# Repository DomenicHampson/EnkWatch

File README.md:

# EnkWatch
<h6>Note: I am still in the process of writing the firmware and mechanical design</h6>
<h4>Custom designed e-ink smartwatch with 2 weeks of battery life! The watch uses a PIC MCU with a built in RTC module and attached to an external temperature and humidity
    sensor via SPI bus to display data to the user on a e-ink screen. The time/date and off-times are set, aswell as the sensors calibrated through USB 2.0 by the user through
    python scripts. The watch is enclosed is a 3D printed shell designed using solidworks.</h4>

<h4><u>Features</u></h4>
<ul>
  <li>2 Week Battery Life: Use low power components and efficient firmware to maximize battery life</li>
  <li>Power Switching and Protection: USB power can simulatenously charge the battery and power the watch. Battery overchage protection provided by a management IC and over
      discharge protection via mosfet controlled by the PIC.</li>
  <li>USB 2.0 Communication: User can ineract with the MCU through USB to set the time/date, calibrate the altitude sensor and determine at which times to power down their watch
      (for greater battery life).</li>
</ul>

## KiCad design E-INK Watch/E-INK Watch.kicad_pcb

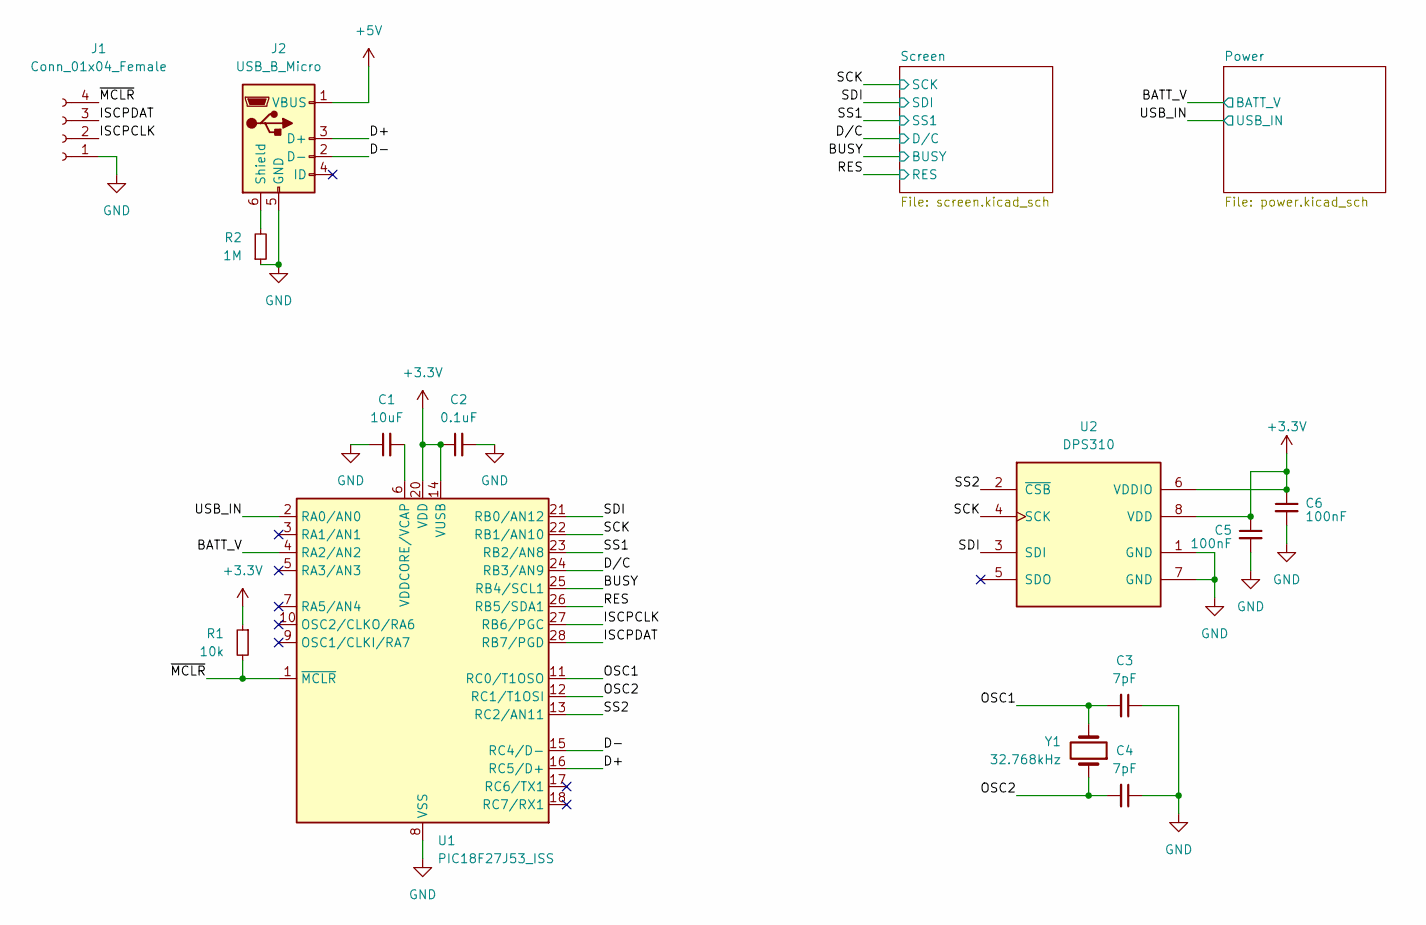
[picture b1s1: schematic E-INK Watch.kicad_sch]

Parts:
C1: 10uF; C_0603_1608Metric_Pad1.08x0.95mm_HandSolder
C2: 0.1uF; C_0603_1608Metric_Pad1.08x0.95mm_HandSolder
C3, C4: 7pF; C_0603_1608Metric_Pad1.08x0.95mm_HandSolder
C5, C6: 100nF; C_0603_1608Metric_Pad1.08x0.95mm_HandSolder
J1: Conn_01x04_Female; HARWIN_M20-7910442R
J2: USB_B_Micro; USB_Micro-B_Molex-105017-0001
R1: 10k; R_0603_1608Metric_Pad0.98x0.95mm_HandSolder
R2: 1M; R_0603_1608Metric_Pad0.98x0.95mm_HandSolder
U1: PIC18F27J53_ISS; SSOP-28_5.3x10.2mm_P0.65mm
U2: DPS310; XDCR_DPS310
Y1: 32.768kHz; XTAL_FC-135R_32.7680KA-AG0

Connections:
+3.3V: C2.1, C5.1, C6.1, R1.1, U1.14 (VUSB), U1.20 (VDD), U2.6 (VDDIO), U2.8 (VDD); also elsewhere on the board
+5V: J2.1 (VBUS); also elsewhere on the board
/BATT_V: U1.4 (RA2/AN2); also elsewhere on the board
/BUSY: U1.25 (RB4/SCL1); also elsewhere on the board
/D+: J2.3 (D+), U1.16 (RC5/D+)
/D-: J2.2 (D-), U1.15 (RC4/D-)
/D/C: U1.24 (RB3/AN9); also elsewhere on the board
/ISCPCLK: J1.2, U1.27 (RB6/PGC)
/ISCPDAT: J1.3, U1.28 (RB7/PGD)
/OSC1: C3.2, U1.11 (RC0/T1OSO), Y1.2
/OSC2: C4.2, U1.12 (RC1/T1OSI), Y1.1
/RES: U1.26 (RB5/SDA1); also elsewhere on the board
/SCK: U1.22 (RB1/AN10), U2.4 (SCK); also elsewhere on the board
/SDI: U1.21 (RB0/AN12), U2.3 (SDI); also elsewhere on the board
/SS1: U1.23 (RB2/AN8); also elsewhere on the board
/SS2: U1.13 (RC2/AN11), U2.2 (~CSB)
/USB_IN: U1.2 (RA0/AN0); also elsewhere on the board
/~MCLR: J1.4, R1.2, U1.1 (~MCLR)
GND: C1.1, C2.2, C3.1, C4.1, C5.2, C6.2, J1.1, J2.5 (GND), R2.1, U1.8 (VSS), U1.19 (VSS), U2.1 (GND), U2.7 (GND); also elsewhere on the board
unnamed: J2.6 (Shield), R2.2
unnamed: C1.2, U1.6 (VDDCORE/VCAP)

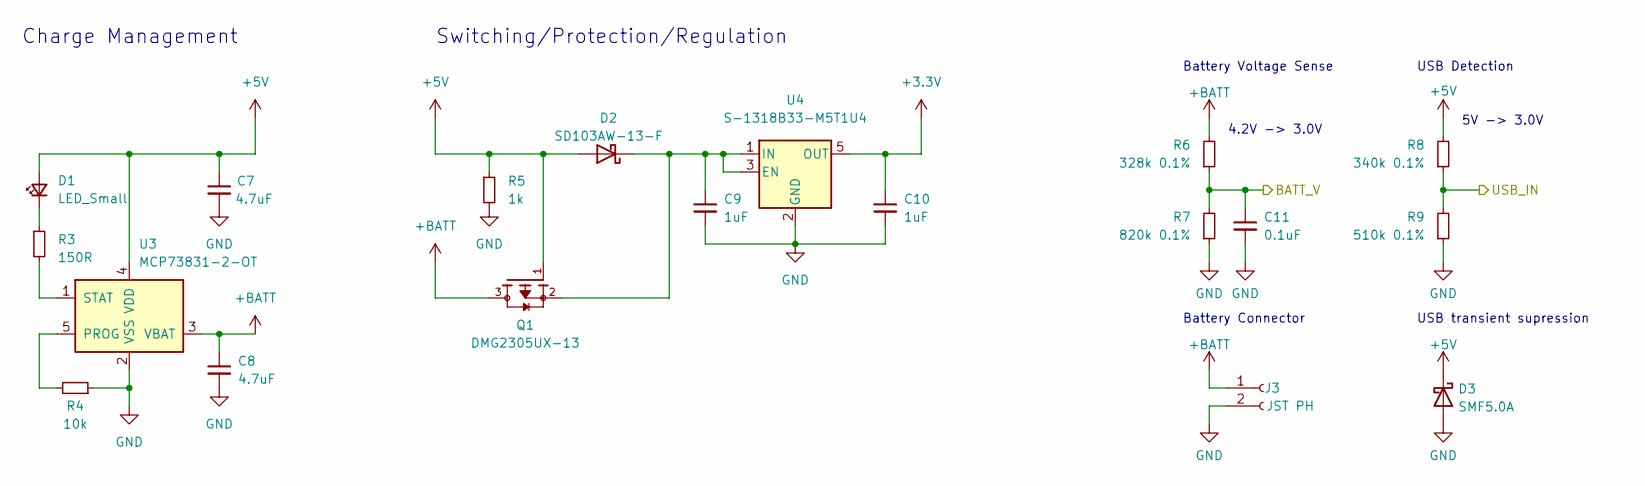
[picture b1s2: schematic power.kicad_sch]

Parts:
C7, C8: 4.7uF; C_0603_1608Metric_Pad1.08x0.95mm_HandSolder
C9, C10: 1uF; C_0603_1608Metric_Pad1.08x0.95mm_HandSolder
C11: 0.1uF; C_0603_1608Metric_Pad1.08x0.95mm_HandSolder
D1: LED_Small; LED_0603_1608Metric_Pad1.05x0.95mm_HandSolder
D2: SD103AW-13-F; D_SOD-123
D3: SMF5.0A; D_SOD-123F
J3: JST PH; JST_PH_S2B-PH-K_1x02_P2.00mm_Horizontal
Q1: DMG2305UX-13; SOT91P240X110-3N; PARTREV 09/2018
R3: 150R; R_0603_1608Metric_Pad0.98x0.95mm_HandSolder
R4: 10k; R_0603_1608Metric_Pad0.98x0.95mm_HandSolder
R5: 1k; R_0603_1608Metric_Pad0.98x0.95mm_HandSolder
R6: 328k 0.1%; R_0603_1608Metric_Pad0.98x0.95mm_HandSolder
R7: 820k 0.1%; R_0603_1608Metric_Pad0.98x0.95mm_HandSolder
R8: 340k 0.1%; R_0603_1608Metric_Pad0.98x0.95mm_HandSolder
R9: 510k 0.1%; R_0603_1608Metric_Pad0.98x0.95mm_HandSolder
U3: MCP73831-2-OT; SOT-23-5
U4: S-1318B33-M5T1U4; SOT-23-5

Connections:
+3.3V: C10.1, U4.5 (OUT); also elsewhere on the board
+5V: C7.1, D1.2 (A), D2.2 (A), D3.1 (K), Q1.1, R5.1, R8.2, U3.4 (VDD); also elsewhere on the board
+BATT: C8.1, J3.1, Q1.3, R6.2, U3.3 (VBAT)
/BATT_V: C11.1, R6.1, R7.2; also elsewhere on the board
/USB_IN: R8.1, R9.2; also elsewhere on the board
GND: C7.2, C8.2, C9.2, C10.2, C11.2, D3.2 (A), J3.2, R4.1, R5.2, R7.1, R9.1, U3.2 (VSS), U4.2 (GND); also elsewhere on the board
unnamed: D1.1 (K), R3.1
unnamed: C9.1, D2.1 (K), Q1.2, U4.1 (IN), U4.3 (EN)
unnamed: R4.2, U3.5 (PROG)
unnamed: R3.2, U3.1 (STAT)

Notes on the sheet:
4.2V -> 3.0V
USB transient supression
Battery Connector
USB Detection
Battery Voltage Sense
Charge Management
5V -> 3.0V
Switching/Protection/Regulation

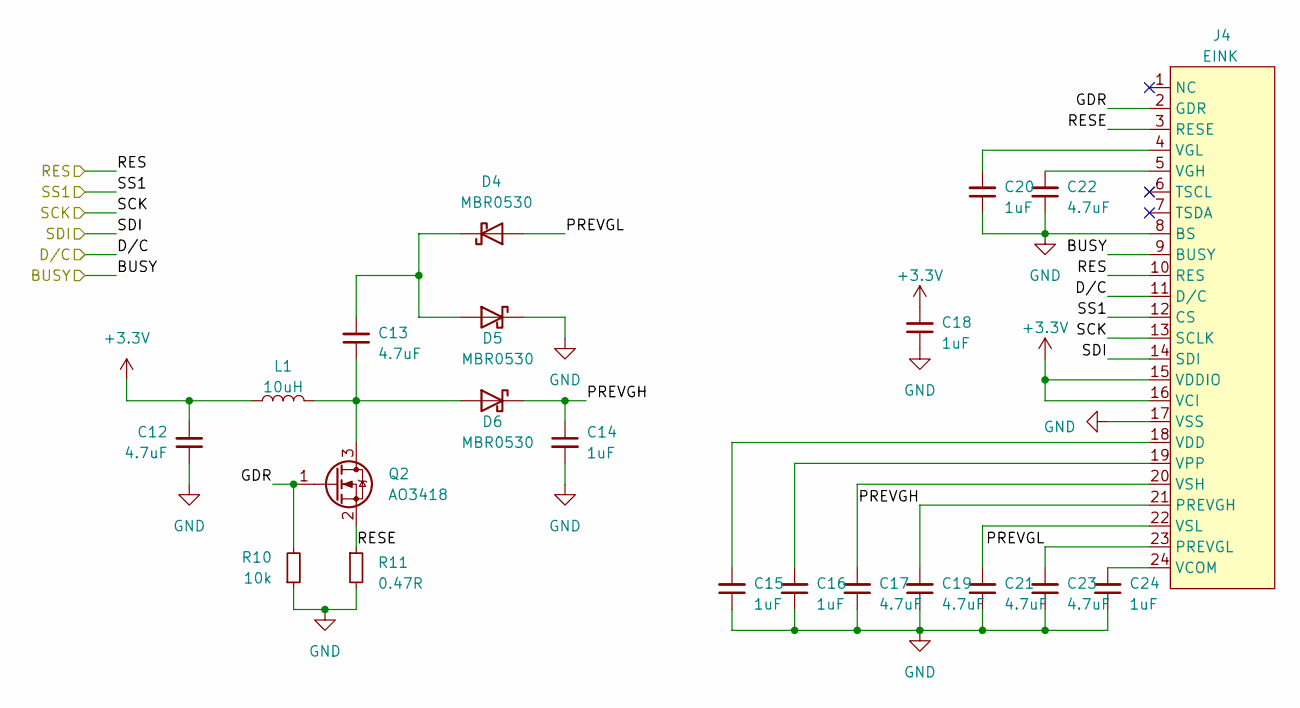
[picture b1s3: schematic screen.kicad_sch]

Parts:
C12, C13, C17, C19, C21, C22, C23: 4.7uF; C_0603_1608Metric_Pad1.08x0.95mm_HandSolder
C14, C15, C16, C18, C20, C24: 1uF; C_0603_1608Metric_Pad1.08x0.95mm_HandSolder
D4, D5, D6: MBR0530; D_SOD-123
J4: EINK; PANASONIC_AYF532435
L1: 10uH; L_1210_3225Metric_Pad1.42x2.65mm_HandSolder
Q2: AO3418; SOT-23
R10: 10k; R_0603_1608Metric_Pad0.98x0.95mm_HandSolder
R11: 0.47R; R_0603_1608Metric_Pad0.98x0.95mm_HandSolder

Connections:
+3.3V: C12.2, C18.2, J4.15 (VDDIO), J4.16 (VCI), L1.1; also elsewhere on the board
/BUSY: J4.9 (BUSY); also elsewhere on the board
/D/C: J4.11 (D/C); also elsewhere on the board
/RES: J4.10 (RES); also elsewhere on the board
/SCK: J4.13 (SCLK); also elsewhere on the board
/SDI: J4.14 (SDI); also elsewhere on the board
/SS1: J4.12 (CS); also elsewhere on the board
/Screen/GDR: J4.2 (GDR), Q2.1 (G), R10.2
/Screen/PREVGH: C14.1, C19.2, D6.1 (K), J4.21 (PREVGH)
/Screen/PREVGL: C23.2, D4.2 (A), J4.23 (PREVGL)
/Screen/RESE: J4.3 (RESE), Q2.2 (S), R11.1
GND: C12.1, C14.2, C15.1, C16.1, C17.1, C18.1, C19.1, C20.1, C21.1, C22.1, C23.1, C24.1, D5.1 (K), J4.8 (BS), J4.17 (VSS), R10.1, R11.2; also elsewhere on the board
unnamed: C13.2, D4.1 (K), D5.2 (A)
unnamed: C13.1, D6.2 (A), L1.2, Q2.3 (D)
unnamed: C24.2, J4.24 (VCOM)
unnamed: C15.2, J4.18 (VDD)
unnamed: C22.2, J4.5 (VGH)
unnamed: C20.2, J4.4 (VGL)
unnamed: C16.2, J4.19 (VPP)
unnamed: C17.2, J4.20 (VSH)
unnamed: C21.2, J4.22 (VSL)

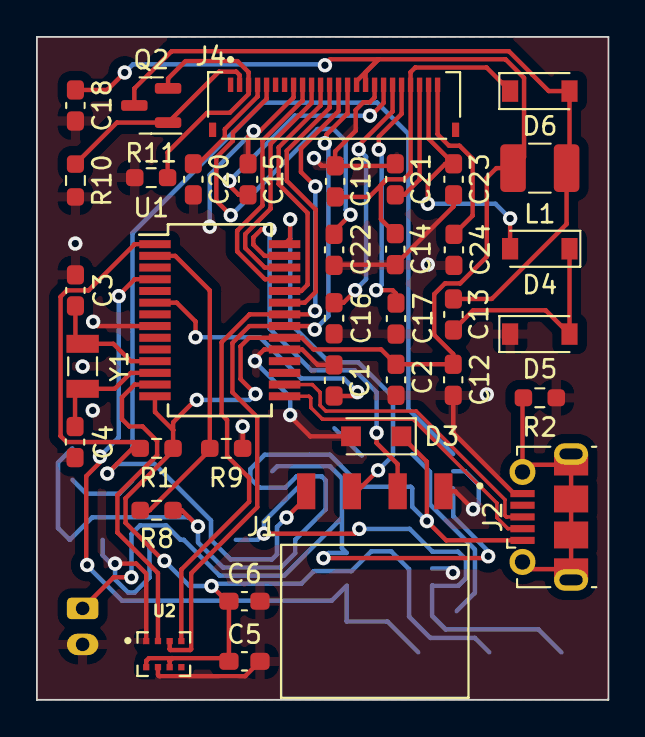
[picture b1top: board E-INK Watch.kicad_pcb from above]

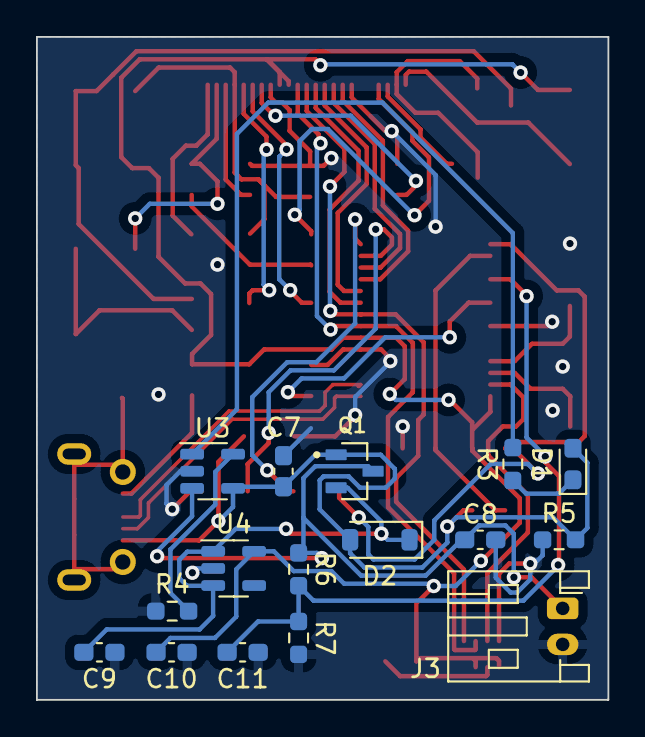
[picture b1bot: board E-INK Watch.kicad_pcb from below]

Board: 2 copper layers, 31.8 x 36.8 mm, 53 parts (16 on the bottom side), 39 nets.

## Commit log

2023-09-13 Added watch schematic and pcb design
2023-09-15 Cleaned up schemtic and pcb
2023-09-16 Small Schematic Modification
2024-05-01 Completed PCB and gerber files
2024-05-01 removed unnecesary gerber files
